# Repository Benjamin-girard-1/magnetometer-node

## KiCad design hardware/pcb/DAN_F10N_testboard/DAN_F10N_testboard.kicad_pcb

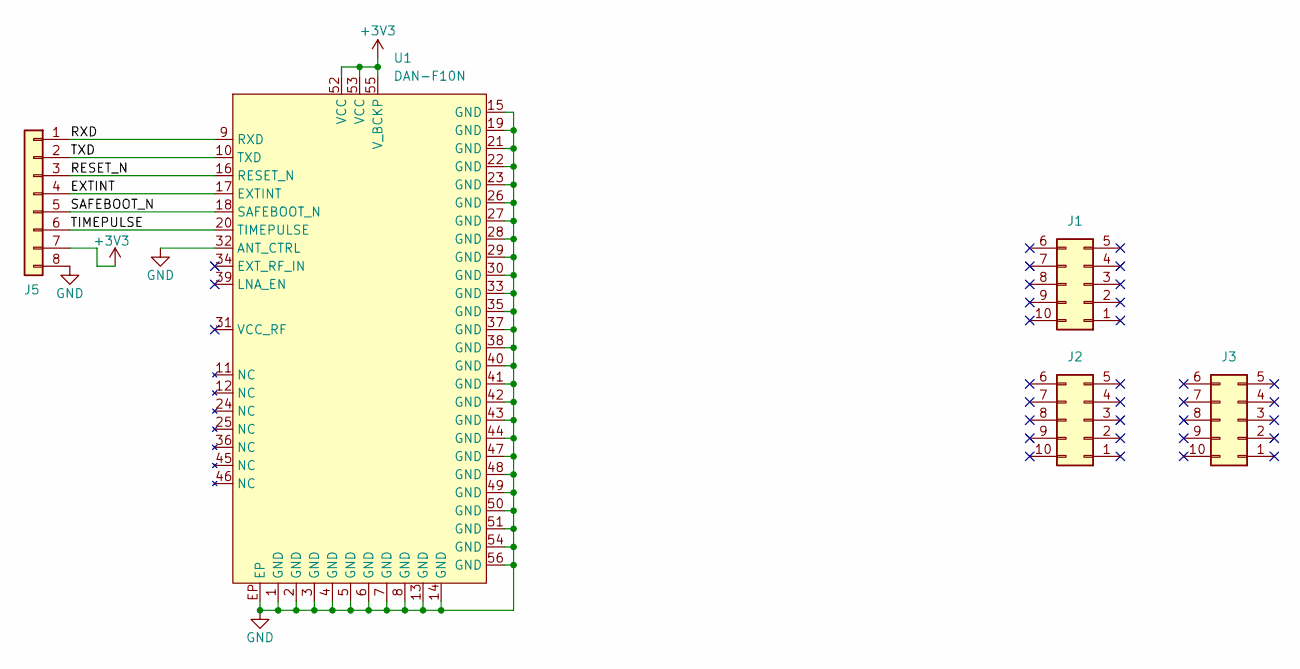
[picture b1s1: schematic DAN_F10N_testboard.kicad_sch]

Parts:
J1, J2, J3: Conn_02x05_Counter_Clockwise; PinHeader_2x05_P2.54mm_Vertical
J5: Conn_01x08; PinHeader_1x08_P2.54mm_Vertical
U1: DAN-F10N; u-blox_DAN-F10N_LCC-56_20x20mm

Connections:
+3V3: J5.7, U1.52 (VCC), U1.53 (VCC), U1.55 (V_BCKP)
/EXTINT: J5.4, U1.17 (EXTINT)
/RESET_N: J5.3, U1.16 (RESET_N)
/RXD: J5.1, U1.9 (RXD)
/SAFEBOOT_N: J5.5, U1.18 (SAFEBOOT_N)
/TIMEPULSE: J5.6, U1.20 (TIMEPULSE)
/TXD: J5.2, U1.10 (TXD)
GND: J5.8, U1.1 (GND), U1.2 (GND), U1.3 (GND), U1.4 (GND), U1.5 (GND), U1.6 (GND), U1.7 (GND), U1.8 (GND), U1.13 (GND), U1.14 (GND), U1.15 (GND), U1.19 (GND), U1.21 (GND), U1.22 (GND), U1.23 (GND), U1.26 (GND), U1.27 (GND), U1.28 (GND), U1.29 (GND), U1.30 (GND), U1.32 (ANT_CTRL), U1.33 (GND), U1.35 (GND), U1.37 (GND), U1.38 (GND), U1.40 (GND), U1.41 (GND), U1.42 (GND), U1.43 (GND), U1.44 (GND), U1.47 (GND), U1.48 (GND), U1.49 (GND), U1.50 (GND), U1.51 (GND), U1.54 (GND), U1.56 (GND), U1.EP

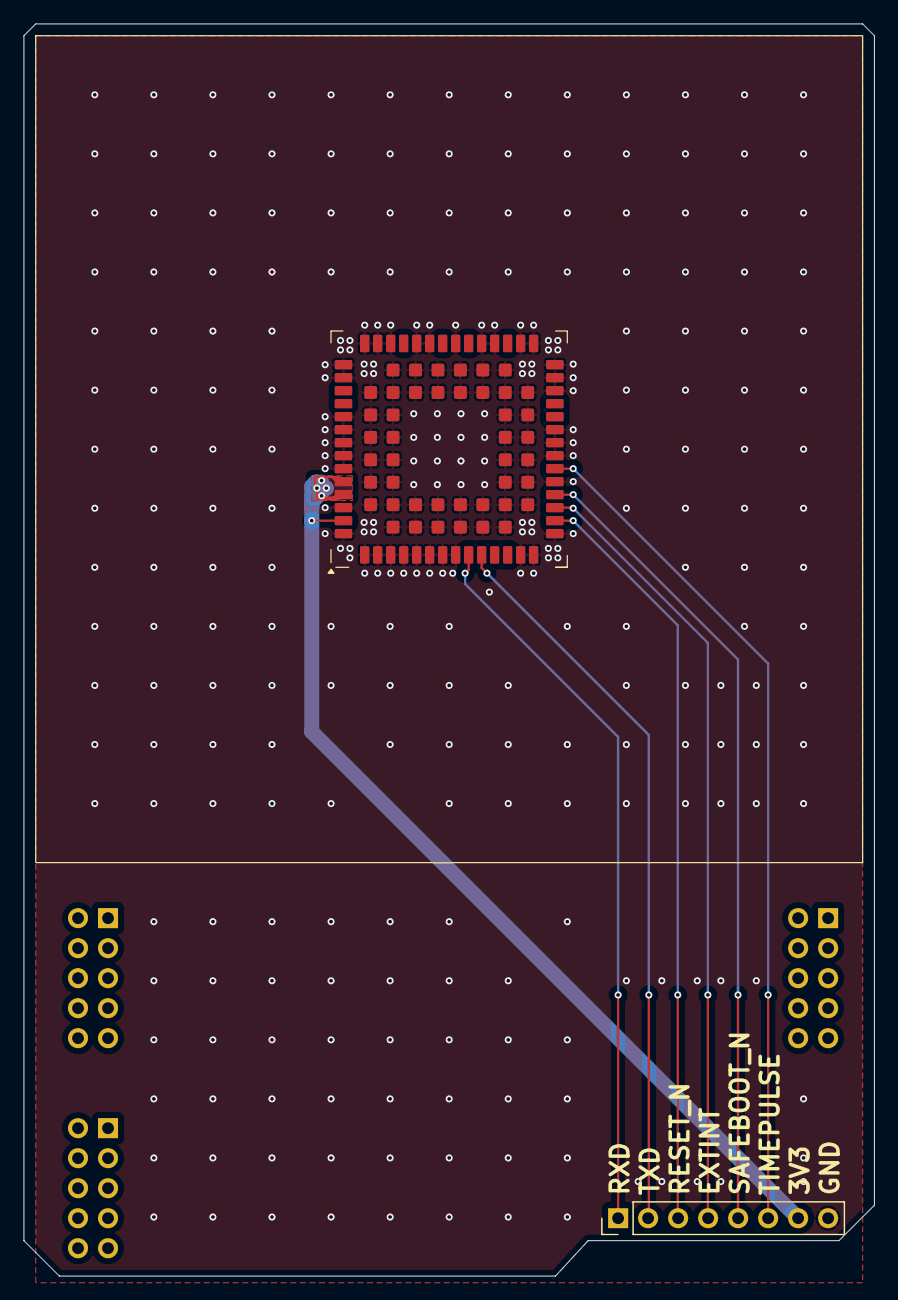
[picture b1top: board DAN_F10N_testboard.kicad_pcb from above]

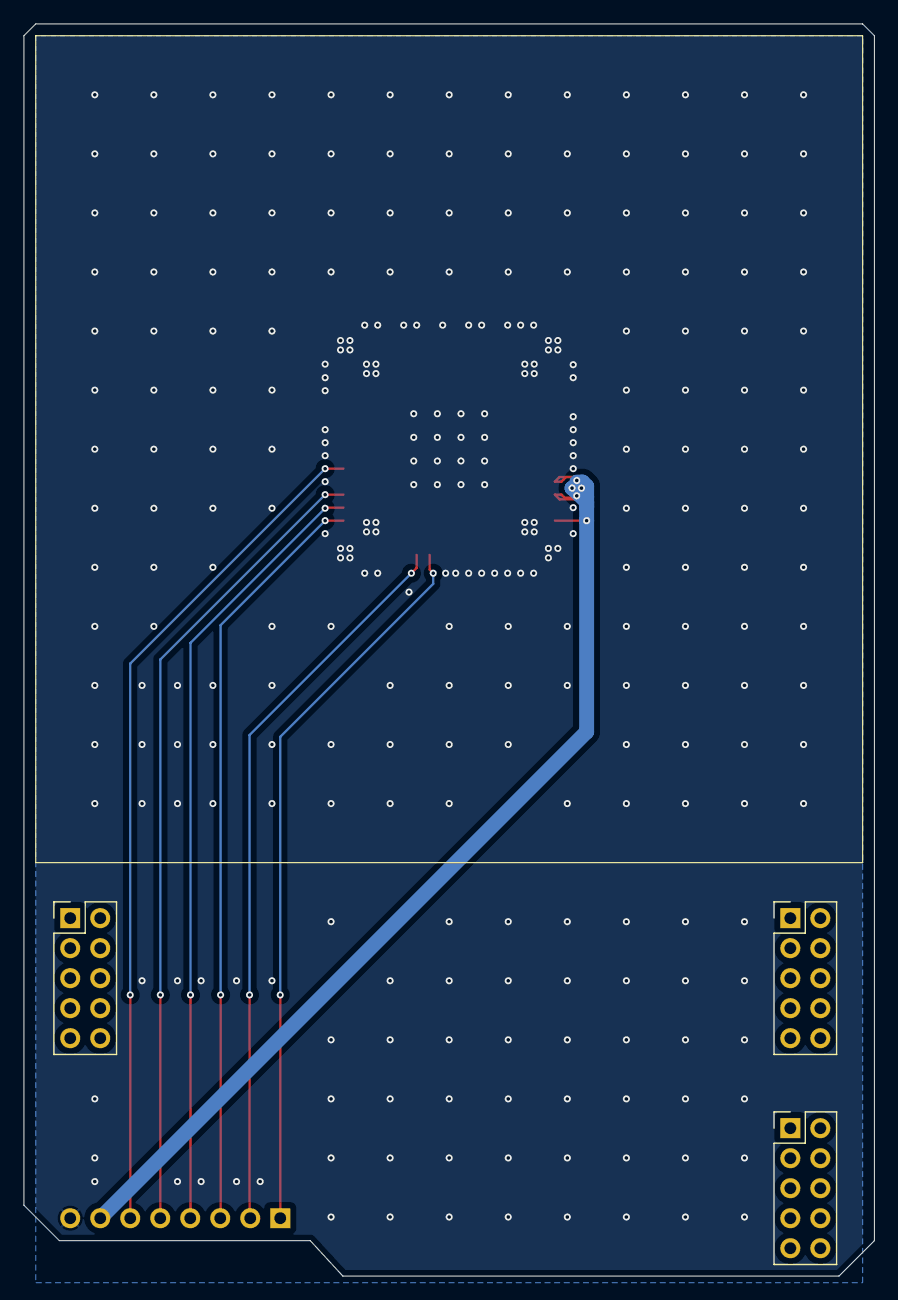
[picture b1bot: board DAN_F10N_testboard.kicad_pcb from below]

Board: 4 copper layers, 72.0 x 106.0 mm, 5 parts (3 on the bottom side), 8 nets.
